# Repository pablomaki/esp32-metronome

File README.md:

# ESP32 metronome

The inspiration for this project was mainly to learn to use freeRTOS (and RTOS in general) and the goal was to create a metronome. 

The project consists of a ESP32 microcontroller, generic rotary encoder, 128x32 OLED screen and an output device, which in my case is a relay driven with a MOSFET. The encoder is used to select the BPM and the signature mode for the metronome while the screen is used to show this information to the user. A circuit diagram/circuit design will be published as well once done.

Each of the components; encoder, output trigger and screen is handled by a separate task that is taken care of by the freeRTOS scheduler.

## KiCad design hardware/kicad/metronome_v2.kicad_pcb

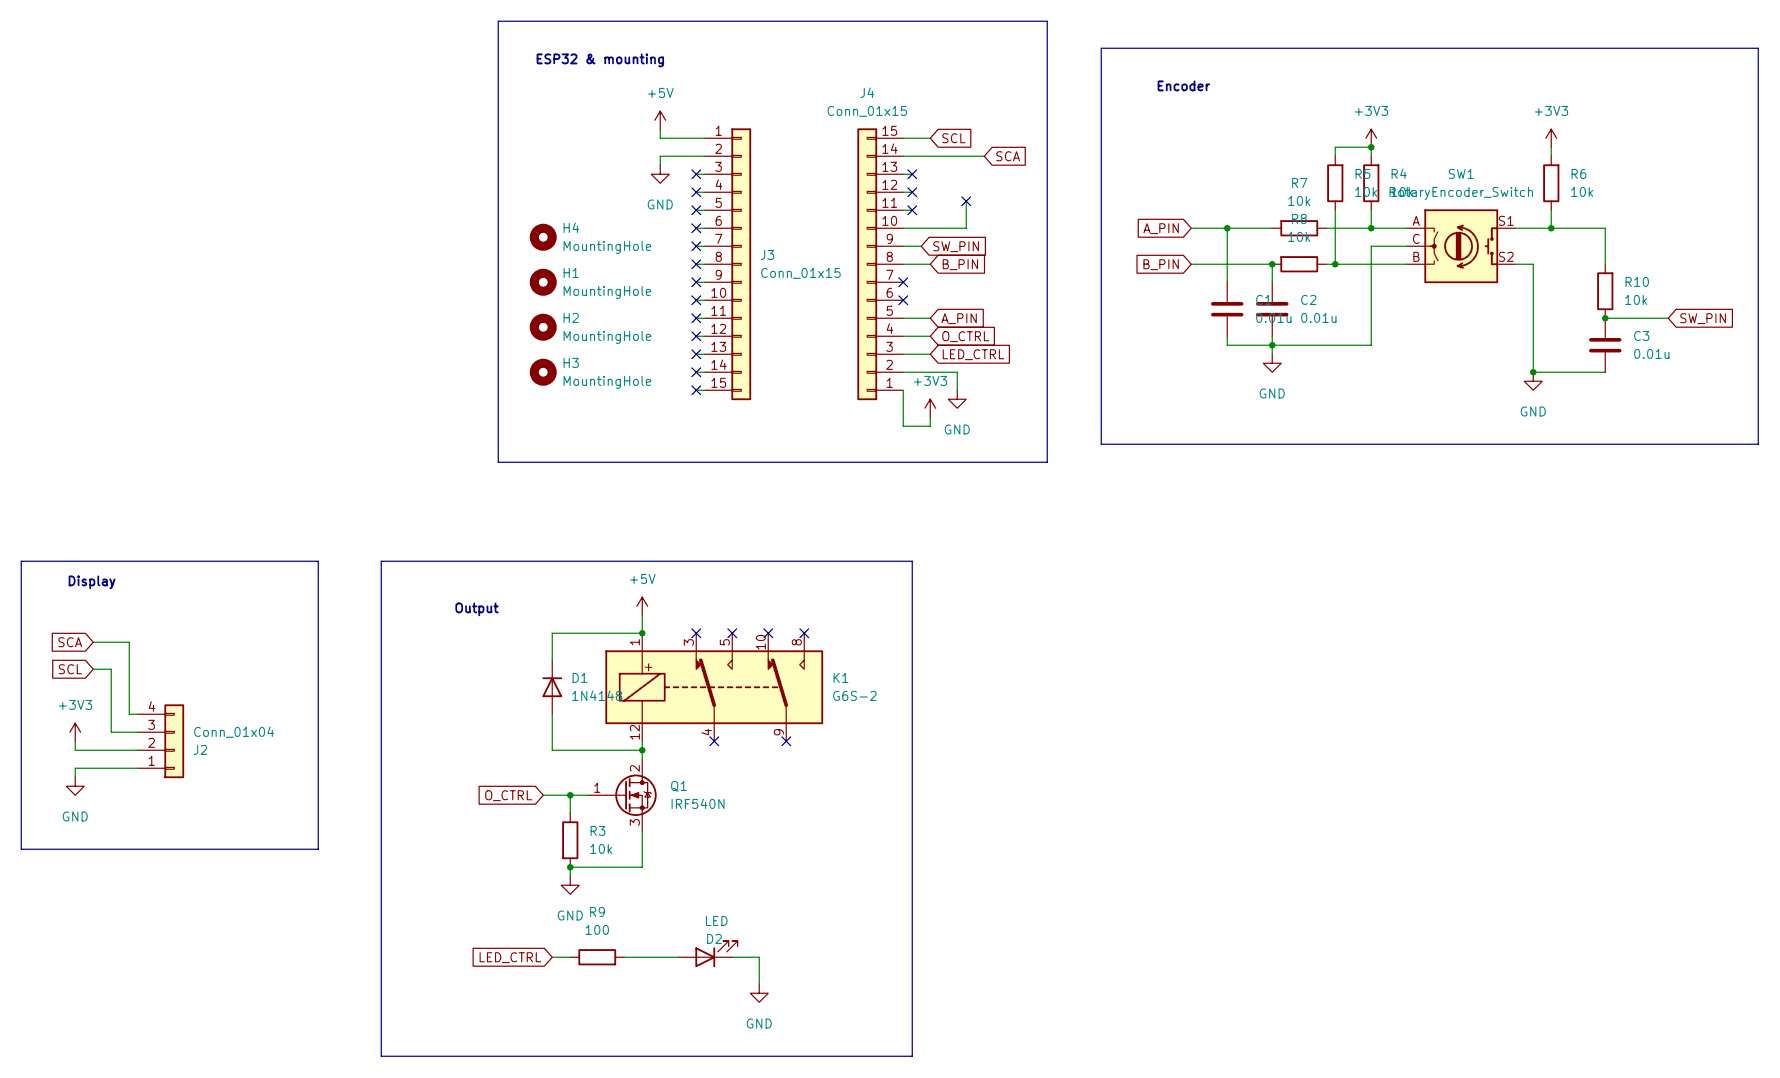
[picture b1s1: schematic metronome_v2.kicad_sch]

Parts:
C1, C2, C3: 0.01u; C_Disc_D5.0mm_W2.5mm_P5.00mm
D1: 1N4148; D_DO-35_SOD27_P7.62mm_Horizontal
D2: LED; LED_D3.0mm
H1, H2, H3, H4: MountingHole; MountingHole_3.2mm_M3_ISO7380
J2: Conn_01x04; PinHeader_1x04_P2.54mm_Vertical
J3, J4: Conn_01x15; PinHeader_1x15_P2.54mm_Vertical
K1: G6S-2; Relay_DPDT_Omron_G6S-2
Q1: IRF540N; TO-220-3_Horizontal_TabDown
R3, R4, R5, R6, R7, R8, R10: 10k; R_Axial_DIN0207_L6.3mm_D2.5mm_P2.54mm_Vertical
R9: 100; R_Axial_DIN0207_L6.3mm_D2.5mm_P2.54mm_Vertical
SW1: RotaryEncoder_Switch; RotaryEncoder_Alps_EC11E-Switch_Vertical_H20mm

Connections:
+3V3: J2.2, J4.1, R4.2, R5.2, R6.2
+5V: D1.1 (K), J3.1, K1.1
A_PIN: C1.1, J4.5, R7.2
B_PIN: C2.1, J4.8, R8.2
GND: C1.2, C2.2, C3.2, D2.1 (K), J2.1, J3.2, J4.2, Q1.3 (S), R3.2, SW1.C, SW1.S2
LED_CTRL: J4.3, R9.1
unnamed: D1.2 (A), K1.12, Q1.2 (D)
unnamed: D2.2 (A), R9.2
unnamed: R4.1, R7.1, SW1.A
unnamed: R5.1, R8.1, SW1.B
unnamed: R6.1, R10.2, SW1.S1
O_CTRL: J4.4, Q1.1 (G), R3.1
SCA: J2.4, J4.14
SCL: J2.3, J4.15
SW_PIN: C3.1, J4.9, R10.1

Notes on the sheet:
Display
Output
ESP32 & mounting
Encoder

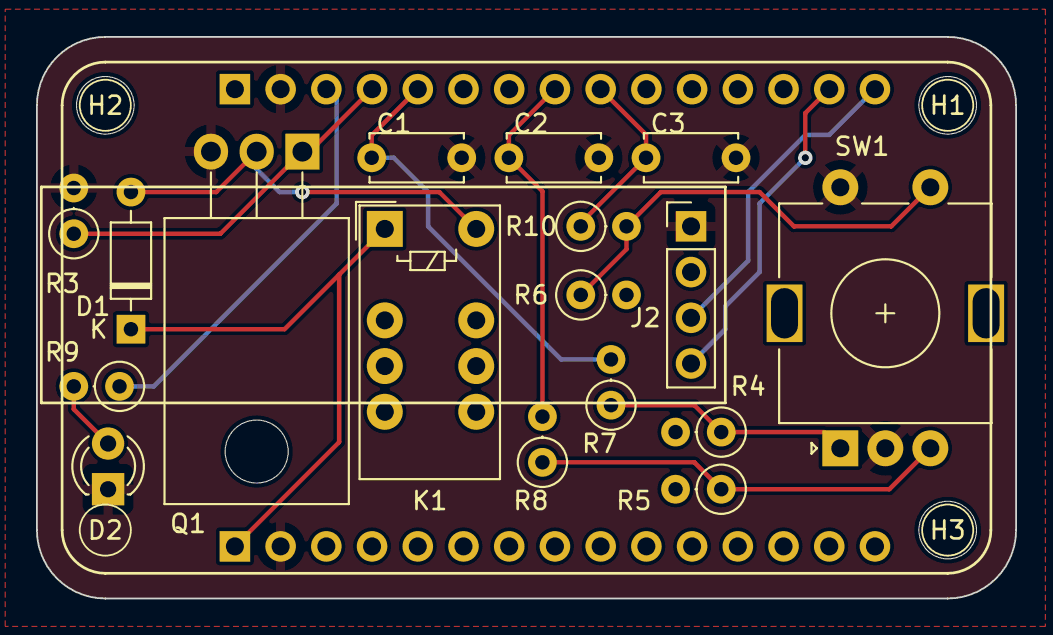
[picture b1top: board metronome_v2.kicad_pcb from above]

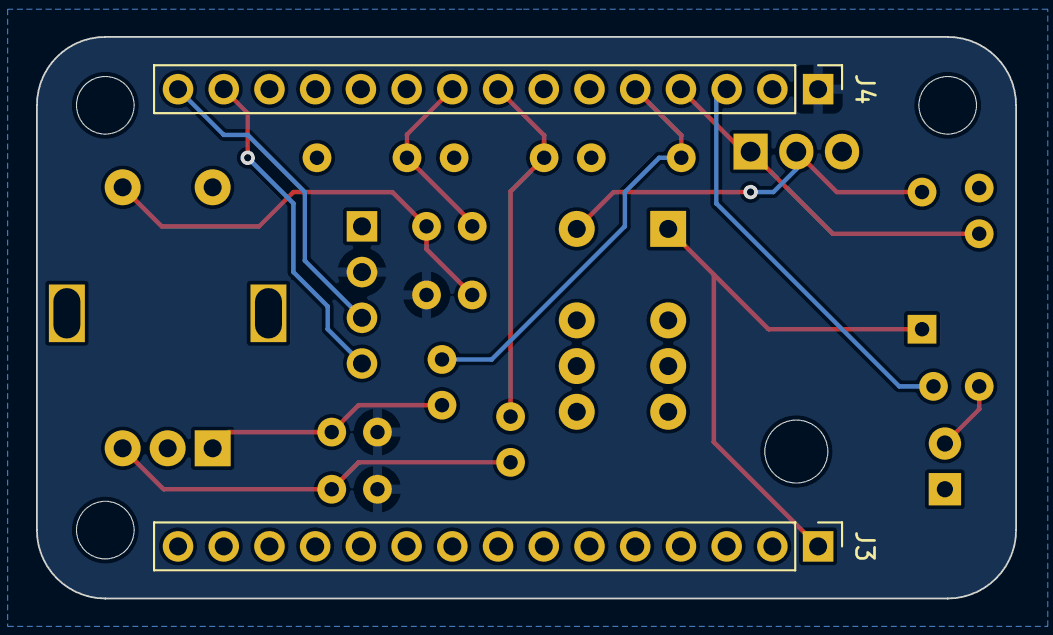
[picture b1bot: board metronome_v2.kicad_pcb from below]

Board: 2 copper layers, 54.4 x 31.2 mm, 22 parts (2 on the bottom side), 15 nets.

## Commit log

2024-10-31 Add existing content to repository
2024-10-31 Update esp-idf-ssd1306 component
2024-12-18 Add pin to flash led at the beginning of a bar
2024-12-18 Change encoder functionality to fit how it should work on the PCB
2024-12-18 Add comments to settings file
2024-12-18 Add possibility to inreverse the screen (rotate 180 deg)
2024-12-18 Add HW design to repository and arrange repository better
2024-12-18 Try fixing the submodule
2024-12-19 Add beat as shared variable and use it
2025-01-17 Arrange hardware folder
2025-01-26 Fix typo in encoder_reader CMakeLists.txt file
2025-01-26 Fallback latest changes for output, add long press for SW_PIN which puts the device to sleep, add handling for sleep mode
2025-01-27 Add WIP standby screen
2025-01-31 Working version
